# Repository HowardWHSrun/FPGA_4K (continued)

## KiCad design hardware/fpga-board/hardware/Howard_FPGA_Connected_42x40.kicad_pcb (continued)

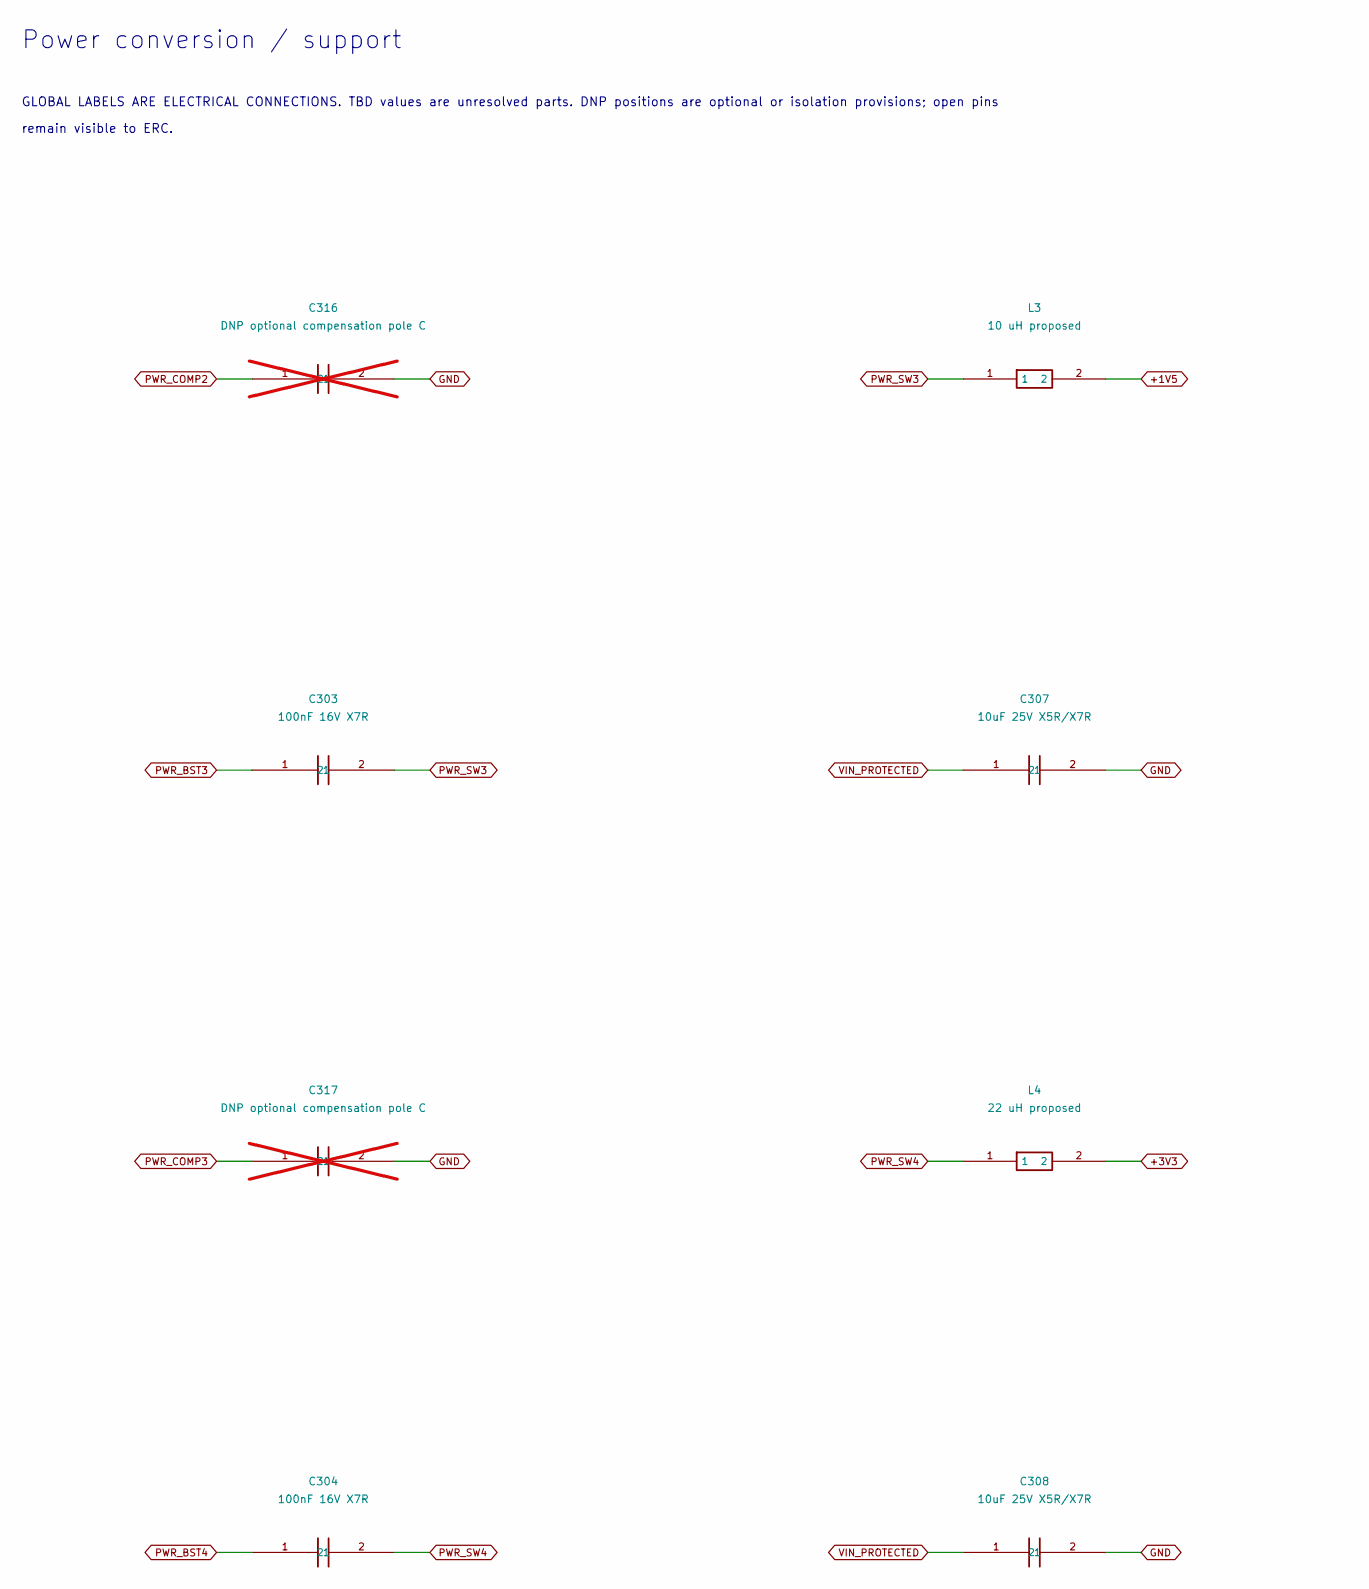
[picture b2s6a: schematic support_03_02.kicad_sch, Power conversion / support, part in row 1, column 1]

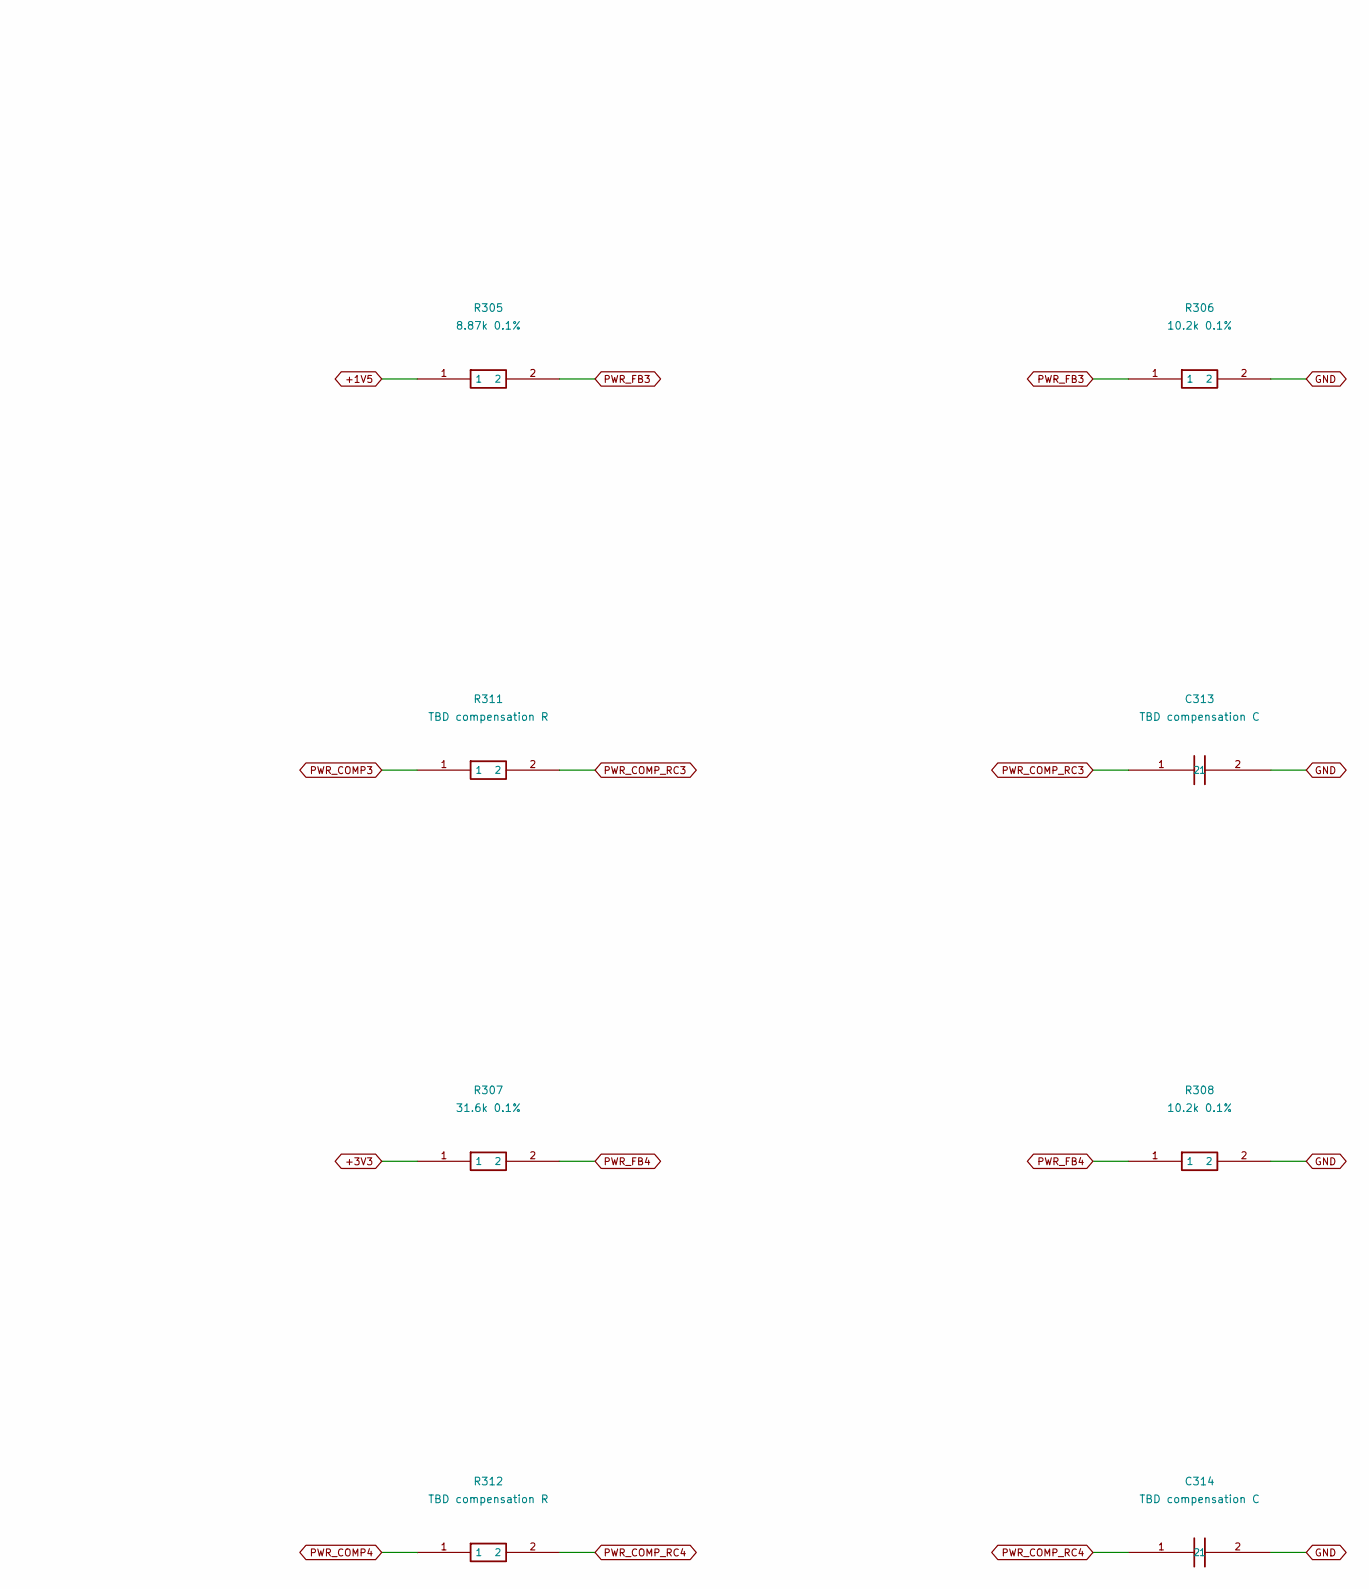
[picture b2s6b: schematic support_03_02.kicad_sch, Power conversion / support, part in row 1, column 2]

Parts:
C303: 100nF 16V X7R; C_0402_1005Metric__C303; Tolerance TBD; Voltage rating TBD; MPN TBD
C304: 100nF 16V X7R; C_0402_1005Metric__C304; Tolerance TBD; Voltage rating TBD; MPN TBD
C307: 10uF 25V X5R/X7R; C_1206_3216Metric__C307; Tolerance TBD; Voltage rating TBD; MPN TBD
C308: 10uF 25V X5R/X7R; C_1206_3216Metric__C308; Tolerance TBD; Voltage rating TBD; MPN TBD
C313: TBD compensation C; C_0402_1005Metric__C313; Tolerance TBD; Voltage rating TBD; MPN TBD
C314: TBD compensation C; C_0402_1005Metric__C314; Tolerance TBD; Voltage rating TBD; MPN TBD
C316: DNP optional compensation pole C; C_0402_1005Metric__C316; Tolerance TBD; Voltage rating TBD; MPN TBD; not fitted
C317: DNP optional compensation pole C; C_0402_1005Metric__C317; Tolerance TBD; Voltage rating TBD; MPN TBD; not fitted
L3: 10 uH proposed; L_Coilcraft_XAL4040-XXX__L3; Tolerance TBD; Voltage rating TBD; MPN XAL4040-103MEC
L4: 22 uH proposed; L_Coilcraft_XAL6060-XXX__L4; Tolerance TBD; Voltage rating TBD; MPN XAL6060-223MEC
R305: 8.87k 0.1%; R_0402_1005Metric__R305; Tolerance TBD; Voltage rating TBD; MPN TBD
R306: 10.2k 0.1%; R_0402_1005Metric__R306; Tolerance TBD; Voltage rating TBD; MPN TBD
R307: 31.6k 0.1%; R_0402_1005Metric__R307; Tolerance TBD; Voltage rating TBD; MPN TBD
R308: 10.2k 0.1%; R_0402_1005Metric__R308; Tolerance TBD; Voltage rating TBD; MPN TBD
R311: TBD compensation R; R_0402_1005Metric__R311; Tolerance TBD; Voltage rating TBD; MPN TBD
R312: TBD compensation R; R_0402_1005Metric__R312; Tolerance TBD; Voltage rating TBD; MPN TBD

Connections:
+1V5: L3.2, R305.1; also elsewhere on the board
+3V3: L4.2, R307.1; also elsewhere on the board
GND: C307.2, C308.2, C313.2, C314.2, C316.2, C317.2, R306.2, R308.2; also elsewhere on the board
PWR_BST3: C303.1; also elsewhere on the board
PWR_BST4: C304.1; also elsewhere on the board
PWR_COMP2: C316.1; also elsewhere on the board
PWR_COMP3: C317.1, R311.1; also elsewhere on the board
PWR_COMP4: R312.1; also elsewhere on the board
PWR_COMP_RC3: C313.1, R311.2
PWR_COMP_RC4: C314.1, R312.2
PWR_FB3: R305.2, R306.1; also elsewhere on the board
PWR_FB4: R307.2, R308.1; also elsewhere on the board
PWR_SW3: C303.2, L3.1; also elsewhere on the board
PWR_SW4: C304.2, L4.1; also elsewhere on the board
VIN_PROTECTED: C307.1, C308.1; also elsewhere on the board

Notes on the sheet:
GLOBAL LABELS ARE ELECTRICAL CONNECTIONS. TBD values are unresolved parts. DNP positions are optional or isolation provisions; open pins
Power conversion / support
remain visible to ERC.

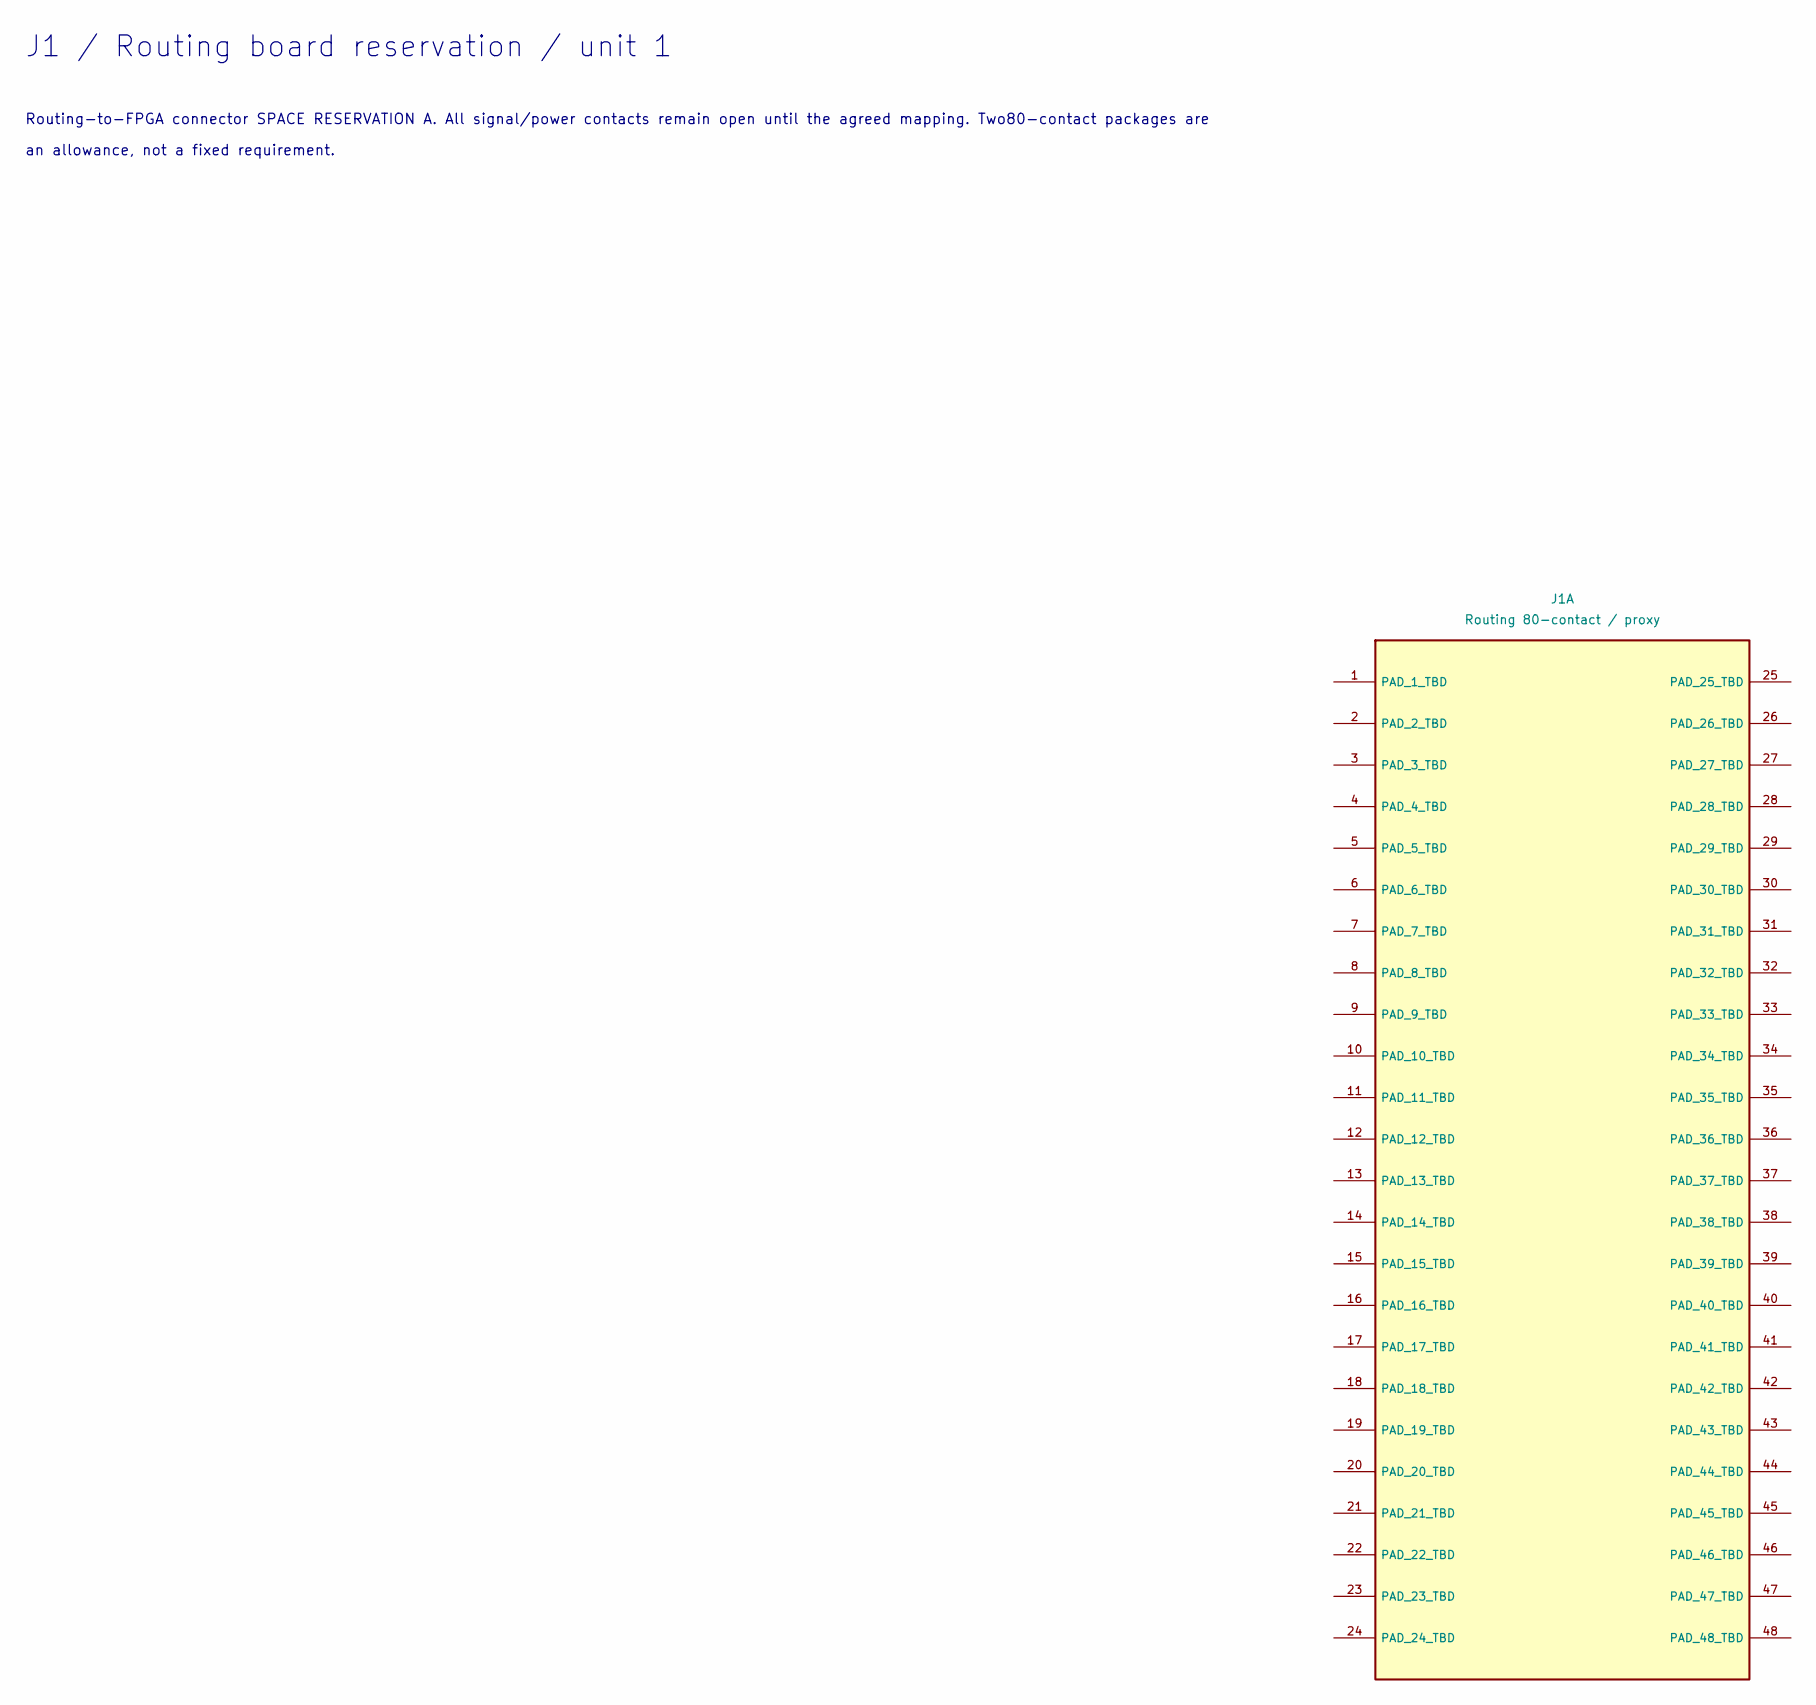
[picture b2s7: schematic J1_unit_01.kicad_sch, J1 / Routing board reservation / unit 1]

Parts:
J1: Routing 80-contact / proxy; Hirose_DF40C-80DS-0.4V_2x40_P0.4mm__J1; Tolerance TBD; Voltage rating TBD; MPN TBD

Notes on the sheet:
Routing-to-FPGA connector SPACE RESERVATION A. All signal/power contacts remain open until the agreed mapping. Two80-contact packages are
J1 / Routing board reservation / unit 1
an allowance, not a fixed requirement.

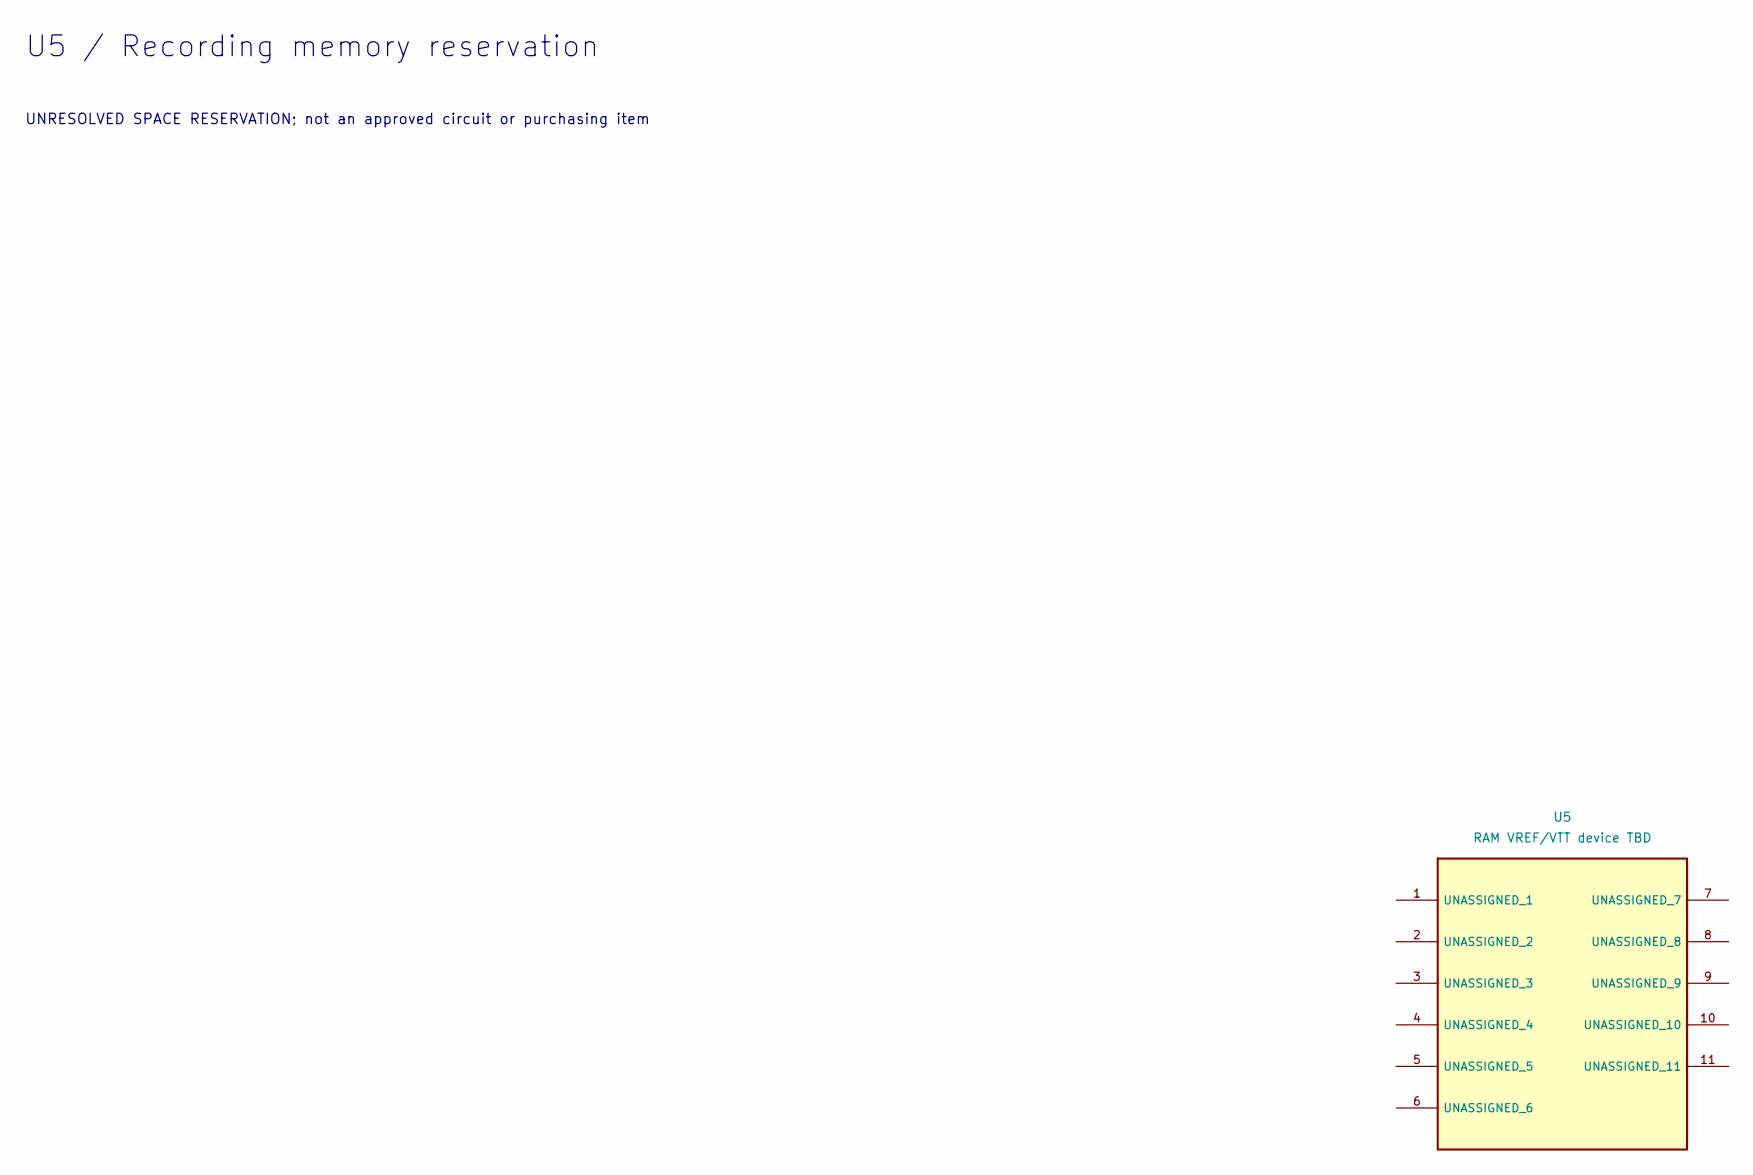
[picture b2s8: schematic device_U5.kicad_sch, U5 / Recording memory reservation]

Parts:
U5: RAM VREF/VTT device TBD; VSON-10-1EP_3x3mm_P0.5mm_EP1.2x2mm__U5; Tolerance TBD; Voltage rating TBD; MPN TBD

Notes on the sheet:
U5 / Recording memory reservation
UNRESOLVED SPACE RESERVATION; not an approved circuit or purchasing item

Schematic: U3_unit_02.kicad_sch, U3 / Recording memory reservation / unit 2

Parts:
U3: Recording RAM / exact part TBD; Micron_FBGA-96_8x14mm_Layout9x16_P0.8mm__U3; Tolerance TBD; Voltage rating TBD; MPN TBD

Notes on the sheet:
are not an approved DDR netlist.
U3 / Recording memory reservation / unit 2
ONE recording-RAM package reservation. Exact device, capacity, signal map, controller and supply/termination requirements TBD. Pad numbers

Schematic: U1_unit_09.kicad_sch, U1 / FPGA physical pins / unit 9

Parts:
U1: XC7A200T-1SBG484C; Xilinx_SBG484__U1; Tolerance TBD; Voltage rating TBD; MPN XC7A200T-1SBG484C

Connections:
+1V0: U1.H8 (VCCINT), U1.H10 (VCCINT), U1.J7 (VCCINT), U1.J9 (VCCINT), U1.K8 (VCCINT), U1.L7 (VCCINT), U1.M8 (VCCINT), U1.N7 (VCCINT), U1.P8 (VCCINT), U1.P10 (VCCINT), U1.R7 (VCCINT), U1.R9 (VCCINT), U1.T8 (VCCINT), U1.T10 (VCCINT); also elsewhere on the board
+1V8: U1.H12 (VCCAUX), U1.K12 (VCCAUX), U1.M12 (VCCAUX), U1.P12 (VCCAUX), U1.R11 (VCCAUX); also elsewhere on the board
+3V3: U1.F12 (VCCO_0), U1.T12 (VCCO_0); also elsewhere on the board
GND: U1.A2 (GND), U1.A3 (GND), U1.A5 (GND), U1.A7 (GND), U1.A9 (GND), U1.A11 (GND), U1.A12 (GND), U1.A22 (GND), U1.AA2 (GND), U1.AA12 (GND), U1.AA22 (GND), U1.AB9 (GND), U1.AB19 (GND), U1.B3 (GND), U1.B12 (GND), U1.B19 (GND), U1.C3 (GND), U1.C6 (GND), U1.C10 (GND), U1.C12 (GND), U1.C16 (GND), U1.D3 (GND), U1.D4 (GND), U1.D8 (GND), U1.D12 (GND), U1.D13 (GND), U1.E4 (GND), U1.E5 (GND), U1.E7 (GND), U1.E9 (GND), U1.E11 (GND), U1.E20 (GND), U1.F11 (GND), U1.F17 (GND); also elsewhere on the board
VCCO_13_TBD: U1.Y10 (VCCO_13); also elsewhere on the board

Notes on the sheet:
U1 / FPGA physical pins / unit 9
bank plan or timing constraints.
Exact XC7A200T SBG484 physical pin map. Boot and core rails are drafted. Unassigned acquisition/link/DDR pins remain open; no completed

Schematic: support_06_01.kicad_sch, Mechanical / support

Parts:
H1: M2 mounting; MountingHole_2.2mm_M2__H1; Tolerance TBD; Voltage rating TBD; MPN Non-plated PCB mounting hole
H2: M2 mounting; MountingHole_2.2mm_M2__H2; Tolerance TBD; Voltage rating TBD; MPN Non-plated PCB mounting hole
H3: M2 mounting; MountingHole_2.2mm_M2__H3; Tolerance TBD; Voltage rating TBD; MPN Non-plated PCB mounting hole
H4: M2 mounting; MountingHole_2.2mm_M2__H4; Tolerance TBD; Voltage rating TBD; MPN Non-plated PCB mounting hole

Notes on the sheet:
GLOBAL LABELS ARE ELECTRICAL CONNECTIONS. TBD values are unresolved parts. DNP positions are optional or isolation provisions; open pins
Mechanical / support
remain visible to ERC.

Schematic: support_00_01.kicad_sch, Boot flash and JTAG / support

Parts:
J4: JTAG_CUSTOM_2x3_1.27mm; PinHeader_2x03_P1.27mm_Vertical__J4; Tolerance TBD; Voltage rating TBD; MPN TBD
R101: 4.7kOhm; R_0201_0603Metric__R101; Tolerance 1%; Voltage rating 30 V limiting voltage; MPN CRCW02014K70FKED
R102: 4.7kOhm; R_0201_0603Metric__R102; Tolerance 1%; Voltage rating 30 V limiting voltage; MPN CRCW02014K70FKED
R103: 10kOhm; R_0201_0603Metric__R103; Tolerance 1%; Voltage rating 30 V limiting voltage; MPN CRCW020110K0FKED
R104: 4.7kOhm; R_0201_0603Metric__R104; Tolerance 1%; Voltage rating 30 V limiting voltage; MPN CRCW02014K70FKED
R105: 4.7kOhm; R_0201_0603Metric__R105; Tolerance 1%; Voltage rating 30 V limiting voltage; MPN CRCW02014K70FKED
R106: 4.7kOhm; R_0201_0603Metric__R106; Tolerance 1%; Voltage rating 30 V limiting voltage; MPN CRCW02014K70FKED
R107: 1kOhm; R_0201_0603Metric__R107; Tolerance 1%; Voltage rating 30 V limiting voltage; MPN CRCW02011K00FKED
R108: 1kOhm; R_0201_0603Metric__R108; Tolerance 1%; Voltage rating 30 V limiting voltage; MPN CRCW02011K00FKED
R109: 1kOhm; R_0201_0603Metric__R109; Tolerance 1%; Voltage rating 30 V limiting voltage; MPN CRCW02011K00FKED
R110: 1kOhm; R_0201_0603Metric__R110; Tolerance 1%; Voltage rating 30 V limiting voltage; MPN CRCW02011K00FKED
R111: 22Ohm; R_0201_0603Metric__R111; Tolerance 1%; Voltage rating 30 V limiting voltage; MPN CRCW020122R0FNED
R112: 0Ohm; R_0201_0603Metric__R112; Tolerance jumper <=50mOhm; Voltage rating 30 V limiting voltage; MPN CRCW02010000Z0ED
R113: 0Ohm; R_0201_0603Metric__R113; Tolerance jumper <=50mOhm; Voltage rating 30 V limiting voltage; MPN CRCW02010000Z0ED
R114: 0Ohm; R_0201_0603Metric__R114; Tolerance jumper <=50mOhm; Voltage rating 30 V limiting voltage; MPN CRCW02010000Z0ED
SW1: PROGRAM_B_RESET; SW_SPST_TL3305A__SW1; Tolerance TBD; Voltage rating TBD; MPN TBD

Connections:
+3V3: J4.1 (VTREF), R101.2, R102.2, R103.2, R104.2, R105.2, R106.2, R107.2, R110.2; also elsewhere on the board
CCLK_FPGA: R111.1; also elsewhere on the board
DONE: R103.1; also elsewhere on the board
GND: J4.2 (GND), R108.2, R109.2, SW1.2 (B); also elsewhere on the board
INIT_B: R102.1; also elsewhere on the board
JTAG_TCK: J4.3 (TCK); also elsewhere on the board
JTAG_TDI: J4.5 (TDI); also elsewhere on the board
JTAG_TDO: J4.6 (TDO); also elsewhere on the board
JTAG_TMS: J4.4 (TMS); also elsewhere on the board
MODE_M0: R107.1; also elsewhere on the board
MODE_M1: R108.1; also elsewhere on the board
MODE_M2: R109.1; also elsewhere on the board
PROGRAM_B: R101.1, SW1.1 (A); also elsewhere on the board
PUDC_B: R110.1; also elsewhere on the board
QSPI_CS_N: R104.1; also elsewhere on the board
QSPI_IO0: R112.2; also elsewhere on the board
QSPI_IO0_FPGA: R112.1; also elsewhere on the board
QSPI_IO1: R113.2; also elsewhere on the board
QSPI_IO1_FPGA: R113.1; also elsewhere on the board
QSPI_IO2: R105.1, R114.2; also elsewhere on the board
QSPI_IO2_FPGA: R114.1; also elsewhere on the board
QSPI_IO3: R106.1; also elsewhere on the board
QSPI_SCK: R111.2; also elsewhere on the board

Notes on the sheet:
GLOBAL LABELS ARE ELECTRICAL CONNECTIONS. TBD values are unresolved parts. DNP positions are optional or isolation provisions; open pins
Boot flash and JTAG / support
remain visible to ERC.

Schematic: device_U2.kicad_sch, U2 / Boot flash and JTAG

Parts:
U2: S25FL256SAGMFI000; SOIC-16W_7.5x10.3mm_P1.27mm__U2; Tolerance TBD; Voltage rating TBD; MPN S25FL256SAGMFI000

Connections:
+3V3: U2.2 (VCC); also elsewhere on the board
GND: U2.10 (VSS); also elsewhere on the board
QSPI_CS_N: U2.7 (CS#); also elsewhere on the board
QSPI_IO0: U2.15 (SI/IO0); also elsewhere on the board
QSPI_IO1: U2.8 (SO/IO1); also elsewhere on the board
QSPI_IO2: U2.9 (WP#/IO2); also elsewhere on the board
QSPI_IO3: U2.1 (HOLD#/IO3); also elsewhere on the board
QSPI_SCK: U2.16 (SCK); also elsewhere on the board

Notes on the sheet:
U2 / Boot flash and JTAG
PROPOSED

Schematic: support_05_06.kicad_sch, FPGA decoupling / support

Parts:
C81: 0.47uF; C_0201_0603Metric__C81; Tolerance 20%; Voltage rating 10 V; MPN C0603X5R1A474M030BC
C82: 0.47uF; C_0201_0603Metric__C82; Tolerance 20%; Voltage rating 10 V; MPN C0603X5R1A474M030BC
C83: 47uF; C_1210_3225Metric__C83; Tolerance TBD; Voltage rating TBD; MPN TBD
C84: 100nF; C_0402_1005Metric__C84; Tolerance 10%; Voltage rating 16 V; MPN C1005X7R1C104K050BC

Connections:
+1V8: C84.1; also elsewhere on the board
GND: C81.2, C82.2, C83.2, C84.2; also elsewhere on the board
VCCO_35_TBD: C81.1, C82.1, C83.1; also elsewhere on the board

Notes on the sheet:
GLOBAL LABELS ARE ELECTRICAL CONNECTIONS. TBD values are unresolved parts. DNP positions are optional or isolation provisions; open pins
FPGA decoupling / support
remain visible to ERC.

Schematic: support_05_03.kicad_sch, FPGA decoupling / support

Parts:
C33: 4.7uF; C_0402_1005Metric__C33; Tolerance 10%; Voltage rating 10 V; MPN C1005X5R1A475K050BC
C34: 4.7uF; C_0402_1005Metric__C34; Tolerance 10%; Voltage rating 10 V; MPN C1005X5R1A475K050BC
C35: 4.7uF; C_0402_1005Metric__C35; Tolerance 10%; Voltage rating 10 V; MPN C1005X5R1A475K050BC
C36: 0.47uF; C_0201_0603Metric__C36; Tolerance 20%; Voltage rating 10 V; MPN C0603X5R1A474M030BC
C37: 0.47uF; C_0201_0603Metric__C37; Tolerance 20%; Voltage rating 10 V; MPN C0603X5R1A474M030BC
C38: 0.47uF; C_0201_0603Metric__C38; Tolerance 20%; Voltage rating 10 V; MPN C0603X5R1A474M030BC
C39: 0.47uF; C_0201_0603Metric__C39; Tolerance 20%; Voltage rating 10 V; MPN C0603X5R1A474M030BC
C40: 0.47uF; C_0201_0603Metric__C40; Tolerance 20%; Voltage rating 10 V; MPN C0603X5R1A474M030BC
C41: 47uF; C_1210_3225Metric__C41; Tolerance TBD; Voltage rating TBD; MPN TBD
C42: 4.7uF; C_0402_1005Metric__C42; Tolerance 10%; Voltage rating 10 V; MPN C1005X5R1A475K050BC
C43: 4.7uF; C_0402_1005Metric__C43; Tolerance 10%; Voltage rating 10 V; MPN C1005X5R1A475K050BC
C44: 0.47uF; C_0201_0603Metric__C44; Tolerance 20%; Voltage rating 10 V; MPN C0603X5R1A474M030BC
C45: 0.47uF; C_0201_0603Metric__C45; Tolerance 20%; Voltage rating 10 V; MPN C0603X5R1A474M030BC
C46: 0.47uF; C_0201_0603Metric__C46; Tolerance 20%; Voltage rating 10 V; MPN C0603X5R1A474M030BC
C47: 0.47uF; C_0201_0603Metric__C47; Tolerance 20%; Voltage rating 10 V; MPN C0603X5R1A474M030BC
C48: 47uF; C_1210_3225Metric__C48; Tolerance TBD; Voltage rating TBD; MPN TBD

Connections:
+1V8: C33.1, C34.1, C35.1, C36.1, C37.1, C38.1, C39.1, C40.1; also elsewhere on the board
+3V3: C41.1; also elsewhere on the board
GND: C33.2, C34.2, C35.2, C36.2, C37.2, C38.2, C39.2, C40.2, C41.2, C42.2, C43.2, C44.2, C45.2, C46.2, C47.2, C48.2; also elsewhere on the board
VCCO_13_TBD: C42.1, C43.1, C44.1, C45.1, C46.1, C47.1, C48.1; also elsewhere on the board

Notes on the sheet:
GLOBAL LABELS ARE ELECTRICAL CONNECTIONS. TBD values are unresolved parts. DNP positions are optional or isolation provisions; open pins
FPGA decoupling / support
remain visible to ERC.

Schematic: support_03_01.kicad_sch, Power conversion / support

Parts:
C301: 100nF 16V X7R; C_0402_1005Metric__C301; Tolerance TBD; Voltage rating TBD; MPN TBD
C302: 100nF 16V X7R; C_0402_1005Metric__C302; Tolerance TBD; Voltage rating TBD; MPN TBD
C305: 10uF 25V X5R/X7R; C_1206_3216Metric__C305; Tolerance TBD; Voltage rating TBD; MPN TBD
C306: 10uF 25V X5R/X7R; C_1206_3216Metric__C306; Tolerance TBD; Voltage rating TBD; MPN TBD
C311: TBD compensation C; C_0402_1005Metric__C311; Tolerance TBD; Voltage rating TBD; MPN TBD
C312: TBD compensation C; C_0402_1005Metric__C312; Tolerance TBD; Voltage rating TBD; MPN TBD
C315: DNP optional compensation pole C; C_0402_1005Metric__C315; Tolerance TBD; Voltage rating TBD; MPN TBD; not fitted
L1: 3.3 uH proposed; L_Coilcraft_XAL6030-XXX__L1; Tolerance TBD; Voltage rating TBD; MPN XAL6030-332MEC
L2: 4.7 uH proposed; L_Coilcraft_XAL6060-XXX__L2; Tolerance TBD; Voltage rating TBD; MPN XAL6060-472MEC
Q1: Si7232DN-T1-GE3 - ONE dual NFET package; Vishay_PowerPAK_1212-8_Dual__Q1; Tolerance TBD; Voltage rating TBD; MPN Si7232DN-T1-GE3
R301: 2.49k 0.1%; R_0402_1005Metric__R301; Tolerance TBD; Voltage rating TBD; MPN TBD
R302: 10k 0.1%; R_0402_1005Metric__R302; Tolerance TBD; Voltage rating TBD; MPN TBD
R303: 12.7k 0.1%; R_0402_1005Metric__R303; Tolerance TBD; Voltage rating TBD; MPN TBD
R304: 10.2k 0.1%; R_0402_1005Metric__R304; Tolerance TBD; Voltage rating TBD; MPN TBD
R309: TBD compensation R; R_0402_1005Metric__R309; Tolerance TBD; Voltage rating TBD; MPN TBD
R310: TBD compensation R; R_0402_1005Metric__R310; Tolerance TBD; Voltage rating TBD; MPN TBD

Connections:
+1V0: L1.2, R301.1; also elsewhere on the board
+1V8: L2.2, R303.1; also elsewhere on the board
GND: C305.2, C306.2, C311.2, C312.2, C315.2, Q1.1 (S1), Q1.3 (S2), R302.2, R304.2; also elsewhere on the board
PWR_BST1: C301.1; also elsewhere on the board
PWR_BST2: C302.1; also elsewhere on the board
PWR_COMP1: C315.1, R309.1; also elsewhere on the board
PWR_COMP2: R310.1; also elsewhere on the board
PWR_COMP_RC1: C311.1, R309.2
PWR_COMP_RC2: C312.1, R310.2
PWR_DL1: Q1.2 (G1); also elsewhere on the board
PWR_DL2: Q1.4 (G2); also elsewhere on the board
PWR_FB1: R301.2, R302.1; also elsewhere on the board
PWR_FB2: R303.2, R304.1; also elsewhere on the board
PWR_SW1: C301.2, L1.1, Q1.6 (D1_[physical_7+8]); also elsewhere on the board
PWR_SW2: C302.2, L2.1, Q1.5 (D2_[physical_5+6]); also elsewhere on the board
VIN_PROTECTED: C305.1, C306.1; also elsewhere on the board

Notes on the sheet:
GLOBAL LABELS ARE ELECTRICAL CONNECTIONS. TBD values are unresolved parts. DNP positions are optional or isolation provisions; open pins
Power conversion / support
remain visible to ERC.

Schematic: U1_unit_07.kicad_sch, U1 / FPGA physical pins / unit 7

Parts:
U1: XC7A200T-1SBG484C; Xilinx_SBG484__U1; Tolerance TBD; Voltage rating TBD; MPN XC7A200T-1SBG484C

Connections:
+3V3: U1.U8 (CFGBVS_0); also elsewhere on the board
CCLK_FPGA: U1.L12 (CCLK_0); also elsewhere on the board
DONE: U1.G11 (DONE_0); also elsewhere on the board
INIT_B: U1.U12 (INIT_B_0); also elsewhere on the board
JTAG_TCK: U1.V12 (TCK_0); also elsewhere on the board
JTAG_TDI: U1.R13 (TDI_0); also elsewhere on the board
JTAG_TDO: U1.U13 (TDO_0); also elsewhere on the board
JTAG_TMS: U1.T13 (TMS_0); also elsewhere on the board
MODE_M0: U1.U11 (M0_0); also elsewhere on the board
MODE_M1: U1.U10 (M1_0); also elsewhere on the board
MODE_M2: U1.U9 (M2_0); also elsewhere on the board
PROGRAM_B: U1.N12 (PROGRAM_B_0); also elsewhere on the board

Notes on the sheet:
bank plan or timing constraints.
U1 / FPGA physical pins / unit 7
Exact XC7A200T SBG484 physical pin map. Boot and core rails are drafted. Unassigned acquisition/link/DDR pins remain open; no completed

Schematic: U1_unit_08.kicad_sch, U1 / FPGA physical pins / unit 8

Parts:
U1: XC7A200T-1SBG484C; Xilinx_SBG484__U1; Tolerance TBD; Voltage rating TBD; MPN XC7A200T-1SBG484C

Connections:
+1V8: U1.K10 (VCCADC_0); also elsewhere on the board
GND: U1.F5 (GND), U1.G5 (GND), U1.G6 (GND), U1.G7 (GND), U1.G8 (GND), U1.G9 (GND), U1.G10 (GND), U1.G12 (GND), U1.G14 (GND), U1.H1 (GND), U1.H7 (GND), U1.H9 (GND), U1.H11 (GND), U1.H21 (GND), U1.J8 (GND), U1.J10 (GND), U1.J12 (GND), U1.J18 (GND), U1.K5 (GND), U1.K7 (GND), U1.K9 (GNDADC_0), U1.K11 (GND), U1.K15 (GND), U1.L2 (GND), U1.L8 (GND), U1.L22 (GND), U1.M7 (GND), U1.M11 (GND), U1.M19 (GND), U1.N6 (GND), U1.N8 (GND), U1.N16 (GND), U1.P3 (GND), U1.P7 (GND), U1.P9 (GND), U1.P11 (GND), U1.P13 (GND), U1.R8 (GND), U1.R10 (GND), U1.R12 (GND), U1.R20 (GND), U1.T7 (GND), U1.T9 (GND), U1.T11 (GND), U1.T17 (GND), U1.U4 (GND), U1.U14 (GND), U1.V1 (GND), U1.V11 (GND), U1.V21 (GND), U1.W8 (GND), U1.W18 (GND), U1.Y5 (GND), U1.Y15 (GND); also elsewhere on the board

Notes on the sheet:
U1 / FPGA physical pins / unit 8
bank plan or timing constraints.
Exact XC7A200T SBG484 physical pin map. Boot and core rails are drafted. Unassigned acquisition/link/DDR pins remain open; no completed

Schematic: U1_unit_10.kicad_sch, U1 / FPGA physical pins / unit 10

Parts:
U1: XC7A200T-1SBG484C; Xilinx_SBG484__U1; Tolerance TBD; Voltage rating TBD; MPN XC7A200T-1SBG484C

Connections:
+1V0: U1.J11 (VCCBRAM), U1.L11 (VCCBRAM), U1.N11 (VCCBRAM); also elsewhere on the board
+3V3: U1.M14 (VCCO_14), U1.P18 (VCCO_14), U1.R15 (VCCO_14), U1.T22 (VCCO_14), U1.U19 (VCCO_14), U1.Y20 (VCCO_14); also elsewhere on the board
VCCO_13_TBD: U1.AA17 (VCCO_13), U1.AB14 (VCCO_13), U1.V16 (VCCO_13), U1.W13 (VCCO_13); also elsewhere on the board
VCCO_15_TBD: U1.G19 (VCCO_15), U1.H16 (VCCO_15), U1.J13 (VCCO_15), U1.K20 (VCCO_15), U1.L17 (VCCO_15), U1.N21 (VCCO_15); also elsewhere on the board
VCCO_16_TBD: U1.A17 (VCCO_16), U1.B14 (VCCO_16), U1.C21 (VCCO_16), U1.D18 (VCCO_16), U1.E15 (VCCO_16), U1.F22 (VCCO_16); also elsewhere on the board
VCCO_34_TBD: U1.AA7 (VCCO_34), U1.AB4 (VCCO_34), U1.R5 (VCCO_34), U1.T2 (VCCO_34), U1.V6 (VCCO_34), U1.W3 (VCCO_34); also elsewhere on the board
VCCO_35_TBD: U1.C1 (VCCO_35), U1.F2 (VCCO_35), U1.H6 (VCCO_35), U1.J3 (VCCO_35), U1.M4 (VCCO_35), U1.N1 (VCCO_35); also elsewhere on the board

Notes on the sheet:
bank plan or timing constraints.
Exact XC7A200T SBG484 physical pin map. Boot and core rails are drafted. Unassigned acquisition/link/DDR pins remain open; no completed
U1 / FPGA physical pins / unit 10

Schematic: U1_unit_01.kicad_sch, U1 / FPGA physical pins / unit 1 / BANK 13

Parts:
U1: XC7A200T-1SBG484C; Xilinx_SBG484__U1; Tolerance TBD; Voltage rating TBD; MPN XC7A200T-1SBG484C

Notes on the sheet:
U1 / FPGA physical pins / unit 1 / BANK 13
bank plan or timing constraints.
Exact XC7A200T SBG484 physical pin map. Boot and core rails are drafted. Unassigned acquisition/link/DDR pins remain open; no completed

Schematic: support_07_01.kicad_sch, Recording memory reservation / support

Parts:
C1011: RAM support value TBD; C_0603_1608Metric__C1011; Tolerance TBD; Voltage rating TBD; MPN TBD
C1012: RAM support value TBD; C_0603_1608Metric__C1012; Tolerance TBD; Voltage rating TBD; MPN TBD
C1013: RAM support value TBD; C_0603_1608Metric__C1013; Tolerance TBD; Voltage rating TBD; MPN TBD
C1014: RAM support value TBD; C_0603_1608Metric__C1014; Tolerance TBD; Voltage rating TBD; MPN TBD
C1015: RAM support value TBD; C_0603_1608Metric__C1015; Tolerance TBD; Voltage rating TBD; MPN TBD
C1016: RAM support value TBD; C_0603_1608Metric__C1016; Tolerance TBD; Voltage rating TBD; MPN TBD
C1017: RAM support value TBD; C_0603_1608Metric__C1017; Tolerance TBD; Voltage rating TBD; MPN TBD
C1018: RAM support value TBD; C_0603_1608Metric__C1018; Tolerance TBD; Voltage rating TBD; MPN TBD
C1019: RAM support value TBD; C_0603_1608Metric__C1019; Tolerance TBD; Voltage rating TBD; MPN TBD
C1020: RAM support value TBD; C_0603_1608Metric__C1020; Tolerance TBD; Voltage rating TBD; MPN TBD
C1021: RAM support value TBD; C_0603_1608Metric__C1021; Tolerance TBD; Voltage rating TBD; MPN TBD
C1022: RAM support value TBD; C_0603_1608Metric__C1022; Tolerance TBD; Voltage rating TBD; MPN TBD
R926: RAM support value TBD; R_0402_1005Metric__R926; Tolerance TBD; Voltage rating TBD; MPN TBD
R927: RAM support value TBD; R_0402_1005Metric__R927; Tolerance TBD; Voltage rating TBD; MPN TBD
R928: RAM support value TBD; R_0402_1005Metric__R928; Tolerance TBD; Voltage rating TBD; MPN TBD
R929: RAM support value TBD; R_0402_1005Metric__R929; Tolerance TBD; Voltage rating TBD; MPN TBD

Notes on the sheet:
GLOBAL LABELS ARE ELECTRICAL CONNECTIONS. TBD values are unresolved parts. DNP positions are optional or isolation provisions; open pins
Recording memory reservation / support
remain visible to ERC.

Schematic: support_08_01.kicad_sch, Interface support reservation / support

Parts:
C1101: Interface/filter capacitance TBD; C_0603_1608Metric__C1101; Tolerance TBD; Voltage rating TBD; MPN TBD
C1102: Interface/filter capacitance TBD; C_0603_1608Metric__C1102; Tolerance TBD; Voltage rating TBD; MPN TBD
C1103: Interface/filter capacitance TBD; C_0603_1608Metric__C1103; Tolerance TBD; Voltage rating TBD; MPN TBD

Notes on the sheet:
GLOBAL LABELS ARE ELECTRICAL CONNECTIONS. TBD values are unresolved parts. DNP positions are optional or isolation provisions; open pins
Interface support reservation / support
remain visible to ERC.

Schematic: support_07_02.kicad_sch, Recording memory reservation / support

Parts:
R930: RAM support value TBD; R_0402_1005Metric__R930; Tolerance TBD; Voltage rating TBD; MPN TBD
R931: RAM support value TBD; R_0402_1005Metric__R931; Tolerance TBD; Voltage rating TBD; MPN TBD
R932: RAM support value TBD; R_0402_1005Metric__R932; Tolerance TBD; Voltage rating TBD; MPN TBD
R933: RAM support value TBD; R_0402_1005Metric__R933; Tolerance TBD; Voltage rating TBD; MPN TBD

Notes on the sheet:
GLOBAL LABELS ARE ELECTRICAL CONNECTIONS. TBD values are unresolved parts. DNP positions are optional or isolation provisions; open pins
Recording memory reservation / support
remain visible to ERC.

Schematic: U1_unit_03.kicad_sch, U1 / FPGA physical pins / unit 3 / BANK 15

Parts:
U1: XC7A200T-1SBG484C; Xilinx_SBG484__U1; Tolerance TBD; Voltage rating TBD; MPN XC7A200T-1SBG484C

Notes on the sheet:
bank plan or timing constraints.
U1 / FPGA physical pins / unit 3 / BANK 15
Exact XC7A200T SBG484 physical pin map. Boot and core rails are drafted. Unassigned acquisition/link/DDR pins remain open; no completed

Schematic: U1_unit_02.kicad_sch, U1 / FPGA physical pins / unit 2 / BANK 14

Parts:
U1: XC7A200T-1SBG484C; Xilinx_SBG484__U1; Tolerance TBD; Voltage rating TBD; MPN XC7A200T-1SBG484C

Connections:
PUDC_B: U1.U22 (IO_L3P_T0_DQS_PUDC_B_14); also elsewhere on the board
QSPI_CS_N: U1.T19 (IO_L6P_T0_FCS_B_14); also elsewhere on the board
QSPI_IO0_FPGA: U1.P22 (IO_L1P_T0_D00_MOSI_14); also elsewhere on the board
QSPI_IO1_FPGA: U1.R22 (IO_L1N_T0_D01_DIN_14); also elsewhere on the board
QSPI_IO2_FPGA: U1.P21 (IO_L2P_T0_D02_14); also elsewhere on the board
QSPI_IO3_FPGA: U1.R21 (IO_L2N_T0_D03_14); also elsewhere on the board

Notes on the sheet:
bank plan or timing constraints.
U1 / FPGA physical pins / unit 2 / BANK 14
Exact XC7A200T SBG484 physical pin map. Boot and core rails are drafted. Unassigned acquisition/link/DDR pins remain open; no completed

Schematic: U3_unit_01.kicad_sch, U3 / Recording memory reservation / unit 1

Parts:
U3: Recording RAM / exact part TBD; Micron_FBGA-96_8x14mm_Layout9x16_P0.8mm__U3; Tolerance TBD; Voltage rating TBD; MPN TBD

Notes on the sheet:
are not an approved DDR netlist.
ONE recording-RAM package reservation. Exact device, capacity, signal map, controller and supply/termination requirements TBD. Pad numbers
U3 / Recording memory reservation / unit 1

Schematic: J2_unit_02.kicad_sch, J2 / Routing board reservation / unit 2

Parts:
J2: Routing 80-contact / proxy; Hirose_DF40C-80DS-0.4V_2x40_P0.4mm__J2; Tolerance TBD; Voltage rating TBD; MPN TBD

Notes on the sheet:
J2 / Routing board reservation / unit 2
and Gerald.
Routing-to-FPGA connector SPACE RESERVATION B. Coordinate carrier revision, grounds, clock/control sharing and power handoff with Zitong
